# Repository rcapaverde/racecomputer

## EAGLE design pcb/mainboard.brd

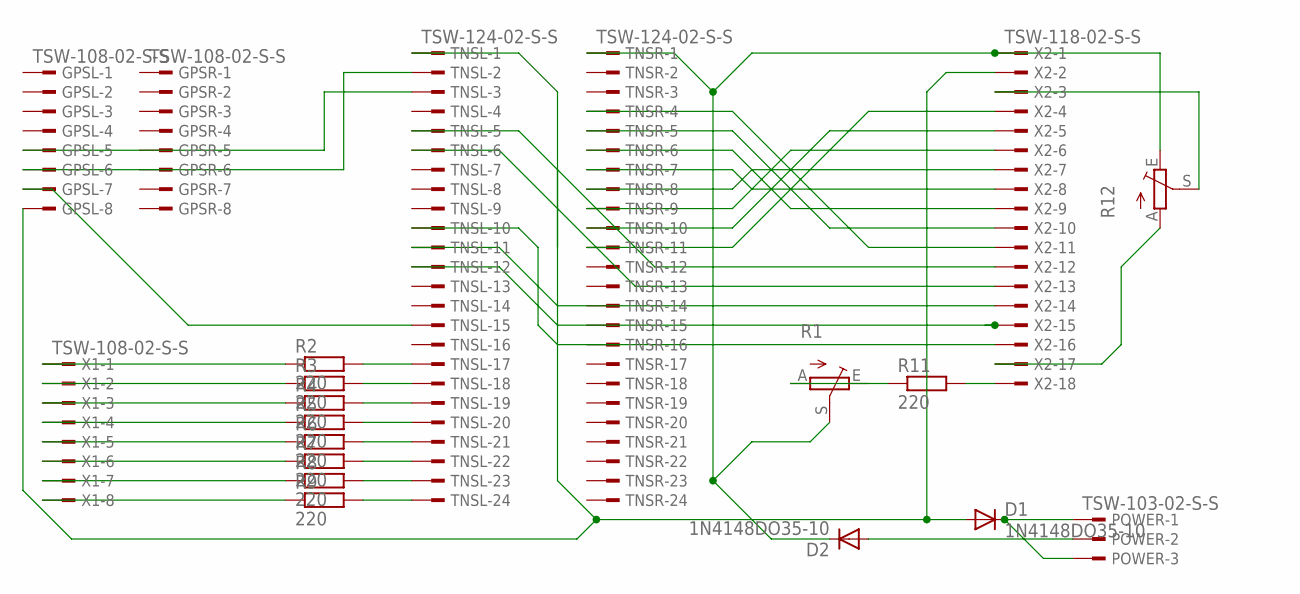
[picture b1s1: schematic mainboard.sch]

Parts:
D1, D2: 1N4148DO35-10; DO35-10
GPSL: TSW-108-02-S-S
GPSR: TSW-108-02-S-S
POWER: TSW-103-02-S-S
R1, R12: TRIM_EU-CA6V; CA6V
R2, R3, R4, R5, R6, R7, R8, R9, R11: 220; 0207/10
TNSL: TSW-124-02-S-S
TNSR: TSW-124-02-S-S
X1: TSW-108-02-S-S
X2: TSW-118-02-S-S

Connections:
GND: D1.A, GPSL.8, TNSL.1, X2.2
unnamed: GPSL.5, TNSL.3
unnamed: R12.S, X2.3
unnamed: GPSL.6, TNSL.2
unnamed: R12.A, X2.17
unnamed: TNSR.11, X2.4
unnamed: TNSR.10, X2.5
unnamed: TNSR.9, X2.6
unnamed: TNSR.8, X2.7
unnamed: TNSR.7, X2.8
unnamed: TNSR.6, X2.9
unnamed: TNSR.5, X2.10
unnamed: TNSR.4, X2.11
unnamed: TNSL.5, X2.12
unnamed: TNSL.6, X2.13
unnamed: TNSL.11, X2.14
unnamed: TNSL.12, X2.15
unnamed: TNSL.10, X2.16
unnamed: R9.2, TNSL.24
unnamed: R8.2, TNSL.23
unnamed: R7.2, TNSL.22
unnamed: R6.2, TNSL.21
unnamed: R5.2, TNSL.20
unnamed: R4.2, TNSL.19
unnamed: R3.2, TNSL.18
unnamed: R2.2, TNSL.17
unnamed: R2.1, X1.1
unnamed: R3.1, X1.2
unnamed: R4.1, X1.3
unnamed: R5.1, X1.4
unnamed: R6.1, X1.5
unnamed: R7.1, X1.6
unnamed: R8.1, X1.7
unnamed: R9.1, X1.8
unnamed: D1.C, POWER.1, POWER.3
unnamed: R1.A, R11.1
unnamed: D2.A, POWER.2
unnamed: R11.2, X2.18
unnamed: GPSL.7, TNSL.15
unnamed: D2.C, R1.S, R12.E, TNSR.1, X2.1

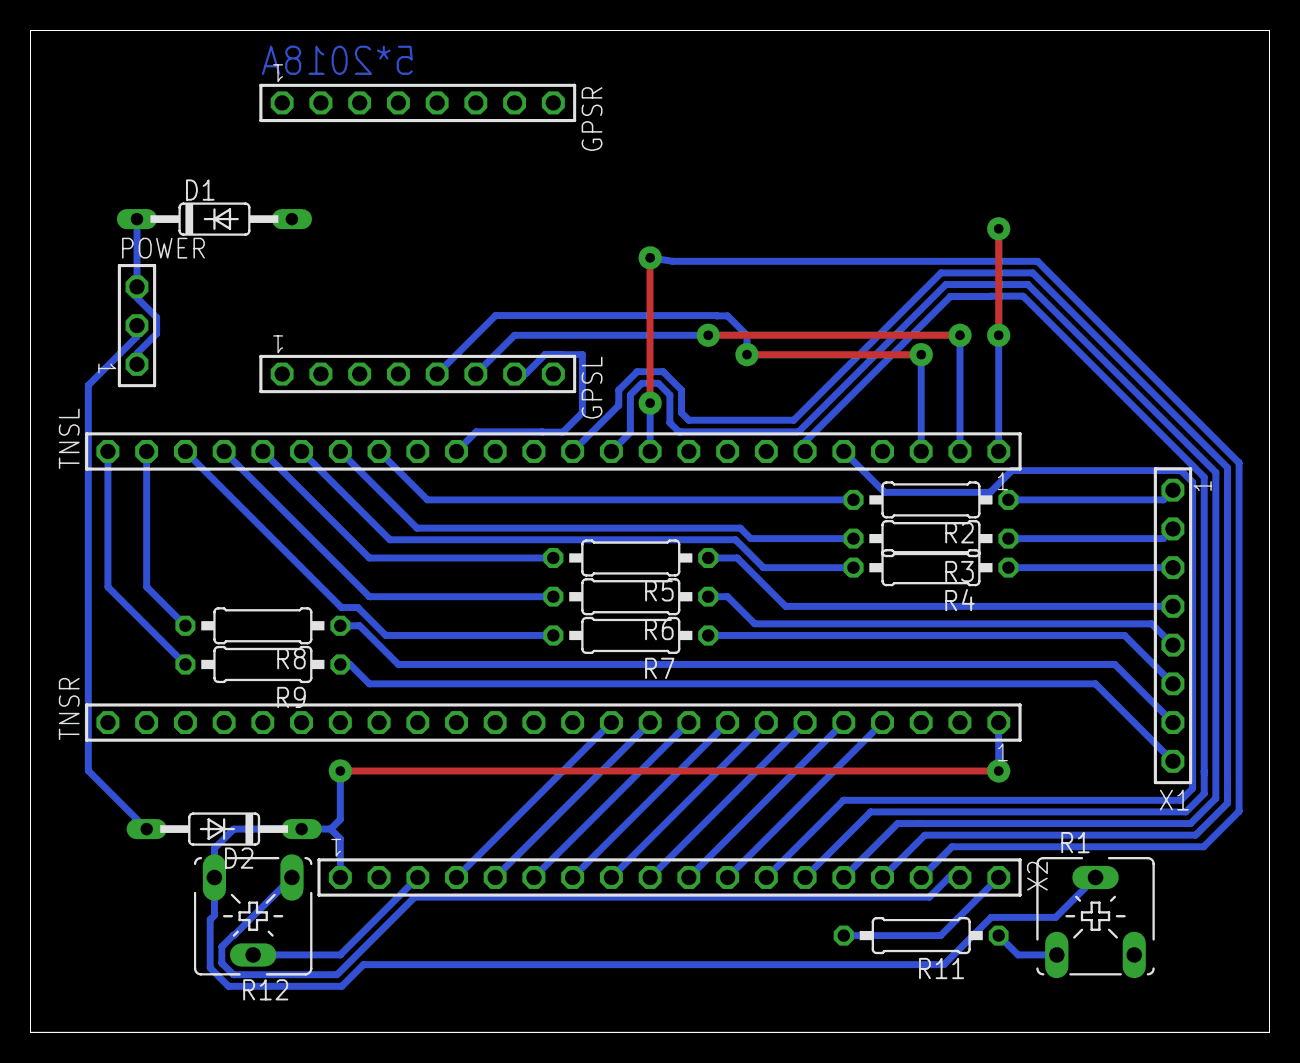
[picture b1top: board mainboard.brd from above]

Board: 2 copper layers, 81.3 x 65.7 mm, 20 parts (0 on the bottom side), 40 nets.

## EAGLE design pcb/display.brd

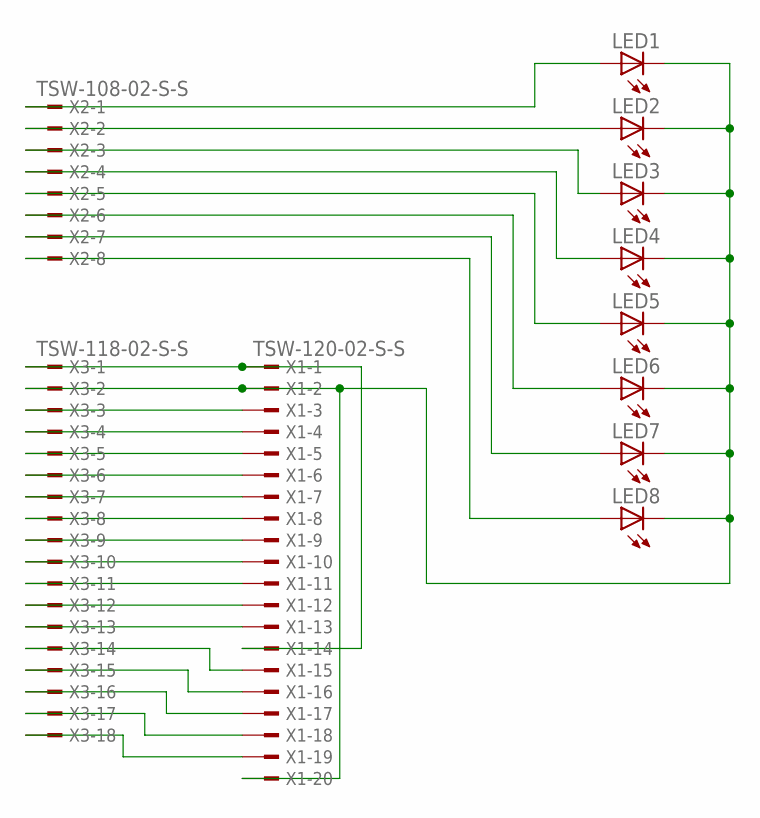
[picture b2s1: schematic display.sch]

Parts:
LED1, LED2, LED3, LED4, LED5, LED6, LED7, LED8: LED_ELD260; LED_LD260
X1: TSW-120-02-S-S
X2: TSW-108-02-S-S
X3: TSW-118-02-S-S

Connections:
GND: LED1.K (C), LED2.K (C), LED3.K (C), LED4.K (C), LED5.K (C), LED6.K (C), LED7.K (C), LED8.K (C), X1.2, X1.20, X3.2
unnamed: X1.1, X1.14, X3.1
unnamed: X1.3, X3.3
unnamed: X1.4, X3.4
unnamed: X1.5, X3.5
unnamed: X1.6, X3.6
unnamed: X1.7, X3.7
unnamed: X1.8, X3.8
unnamed: X1.9, X3.9
unnamed: X1.10, X3.10
unnamed: X1.11, X3.11
unnamed: X1.12, X3.12
unnamed: X1.13, X3.13
unnamed: X1.15, X3.14
unnamed: X1.16, X3.15
unnamed: X1.17, X3.16
unnamed: X1.18, X3.17
unnamed: X1.19, X3.18
unnamed: LED1.A, X2.1
unnamed: LED2.A, X2.2
unnamed: LED3.A, X2.3
unnamed: LED4.A, X2.4
unnamed: LED5.A, X2.5
unnamed: LED6.A, X2.6
unnamed: LED7.A, X2.7
unnamed: LED8.A, X2.8

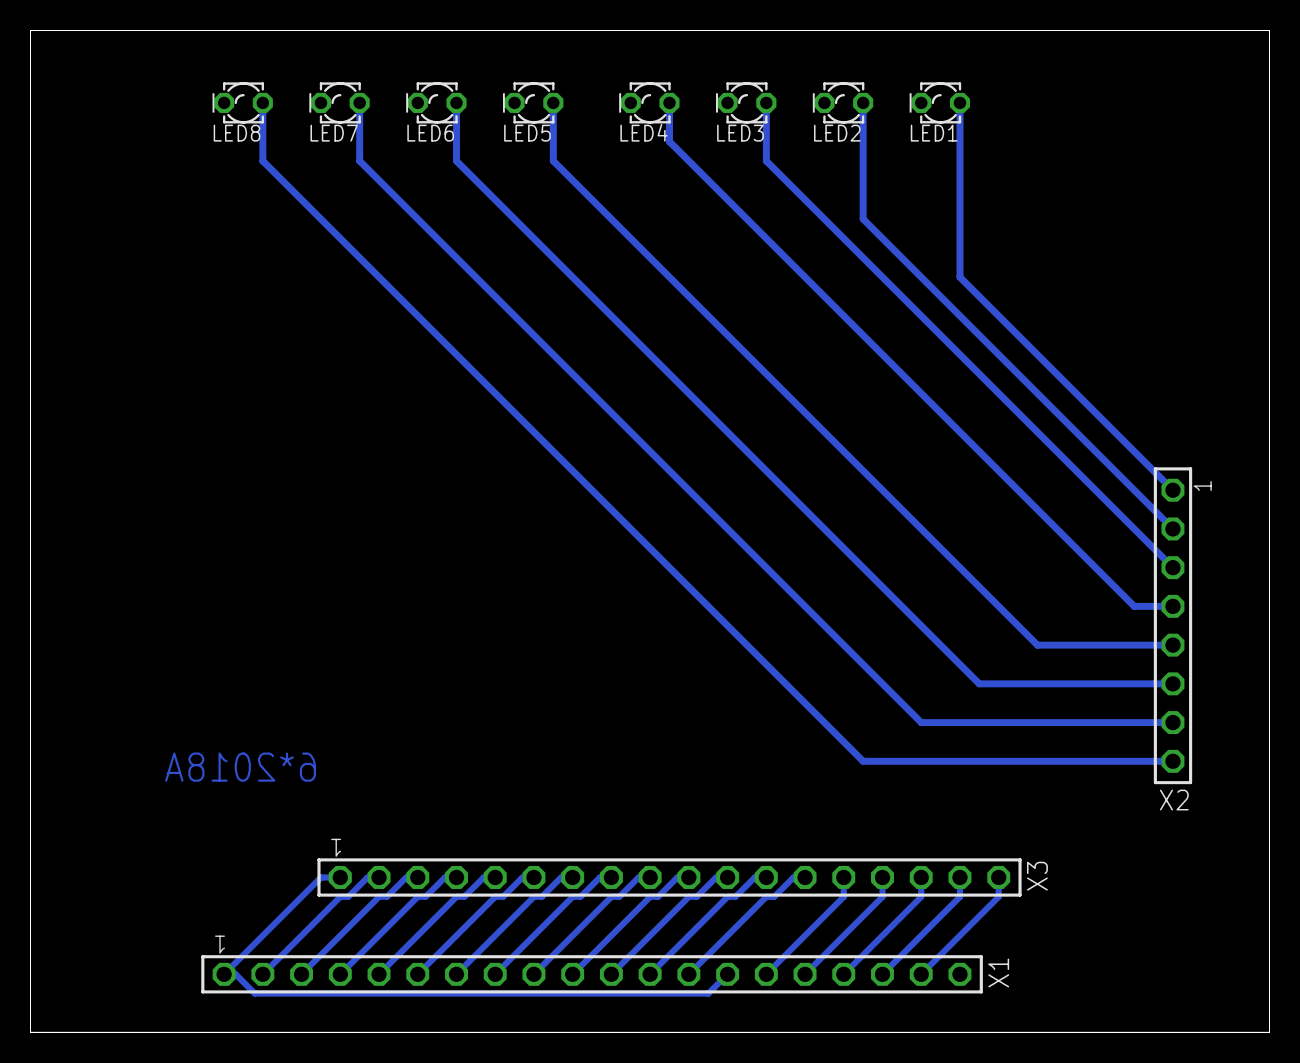
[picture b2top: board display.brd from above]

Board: 2 copper layers, 81.3 x 65.7 mm, 11 parts (0 on the bottom side), 26 nets.

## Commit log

2018-09-22 no message
